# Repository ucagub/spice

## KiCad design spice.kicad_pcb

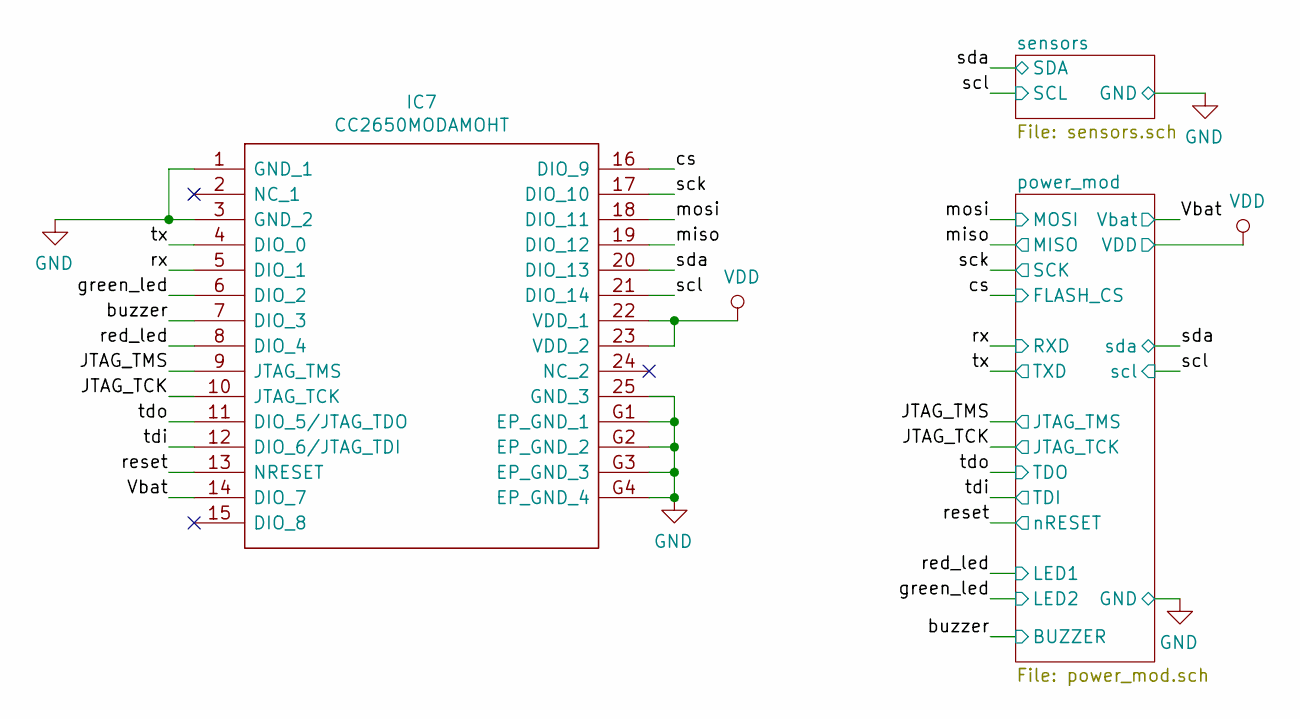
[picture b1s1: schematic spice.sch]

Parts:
IC7: CC2650MODAMOHT

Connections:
/JTAG_TCK: IC7.10 (JTAG_TCK); also elsewhere on the board
/JTAG_TMS: IC7.9 (JTAG_TMS); also elsewhere on the board
/Vbat: IC7.14 (DIO_7); also elsewhere on the board
/buzzer: IC7.7 (DIO_3); also elsewhere on the board
/cs: IC7.16 (DIO_9); also elsewhere on the board
/green_led: IC7.6 (DIO_2); also elsewhere on the board
/miso: IC7.19 (DIO_12); also elsewhere on the board
/mosi: IC7.18 (DIO_11); also elsewhere on the board
/red_led: IC7.8 (DIO_4); also elsewhere on the board
/reset: IC7.13 (NRESET); also elsewhere on the board
/rx: IC7.5 (DIO_1); also elsewhere on the board
/sck: IC7.17 (DIO_10); also elsewhere on the board
/scl: IC7.21 (DIO_14); also elsewhere on the board
/sda: IC7.20 (DIO_13); also elsewhere on the board
/tdi: IC7.12 (DIO_6/JTAG_TDI); also elsewhere on the board
/tdo: IC7.11 (DIO_5/JTAG_TDO); also elsewhere on the board
/tx: IC7.4 (DIO_0); also elsewhere on the board
GND: IC7.1 (GND_1), IC7.3 (GND_2), IC7.25 (GND_3), IC7.G1 (EP_GND_1), IC7.G2 (EP_GND_2), IC7.G3 (EP_GND_3), IC7.G4 (EP_GND_4); also elsewhere on the board
VDD: IC7.22 (VDD_1), IC7.23 (VDD_2); also elsewhere on the board

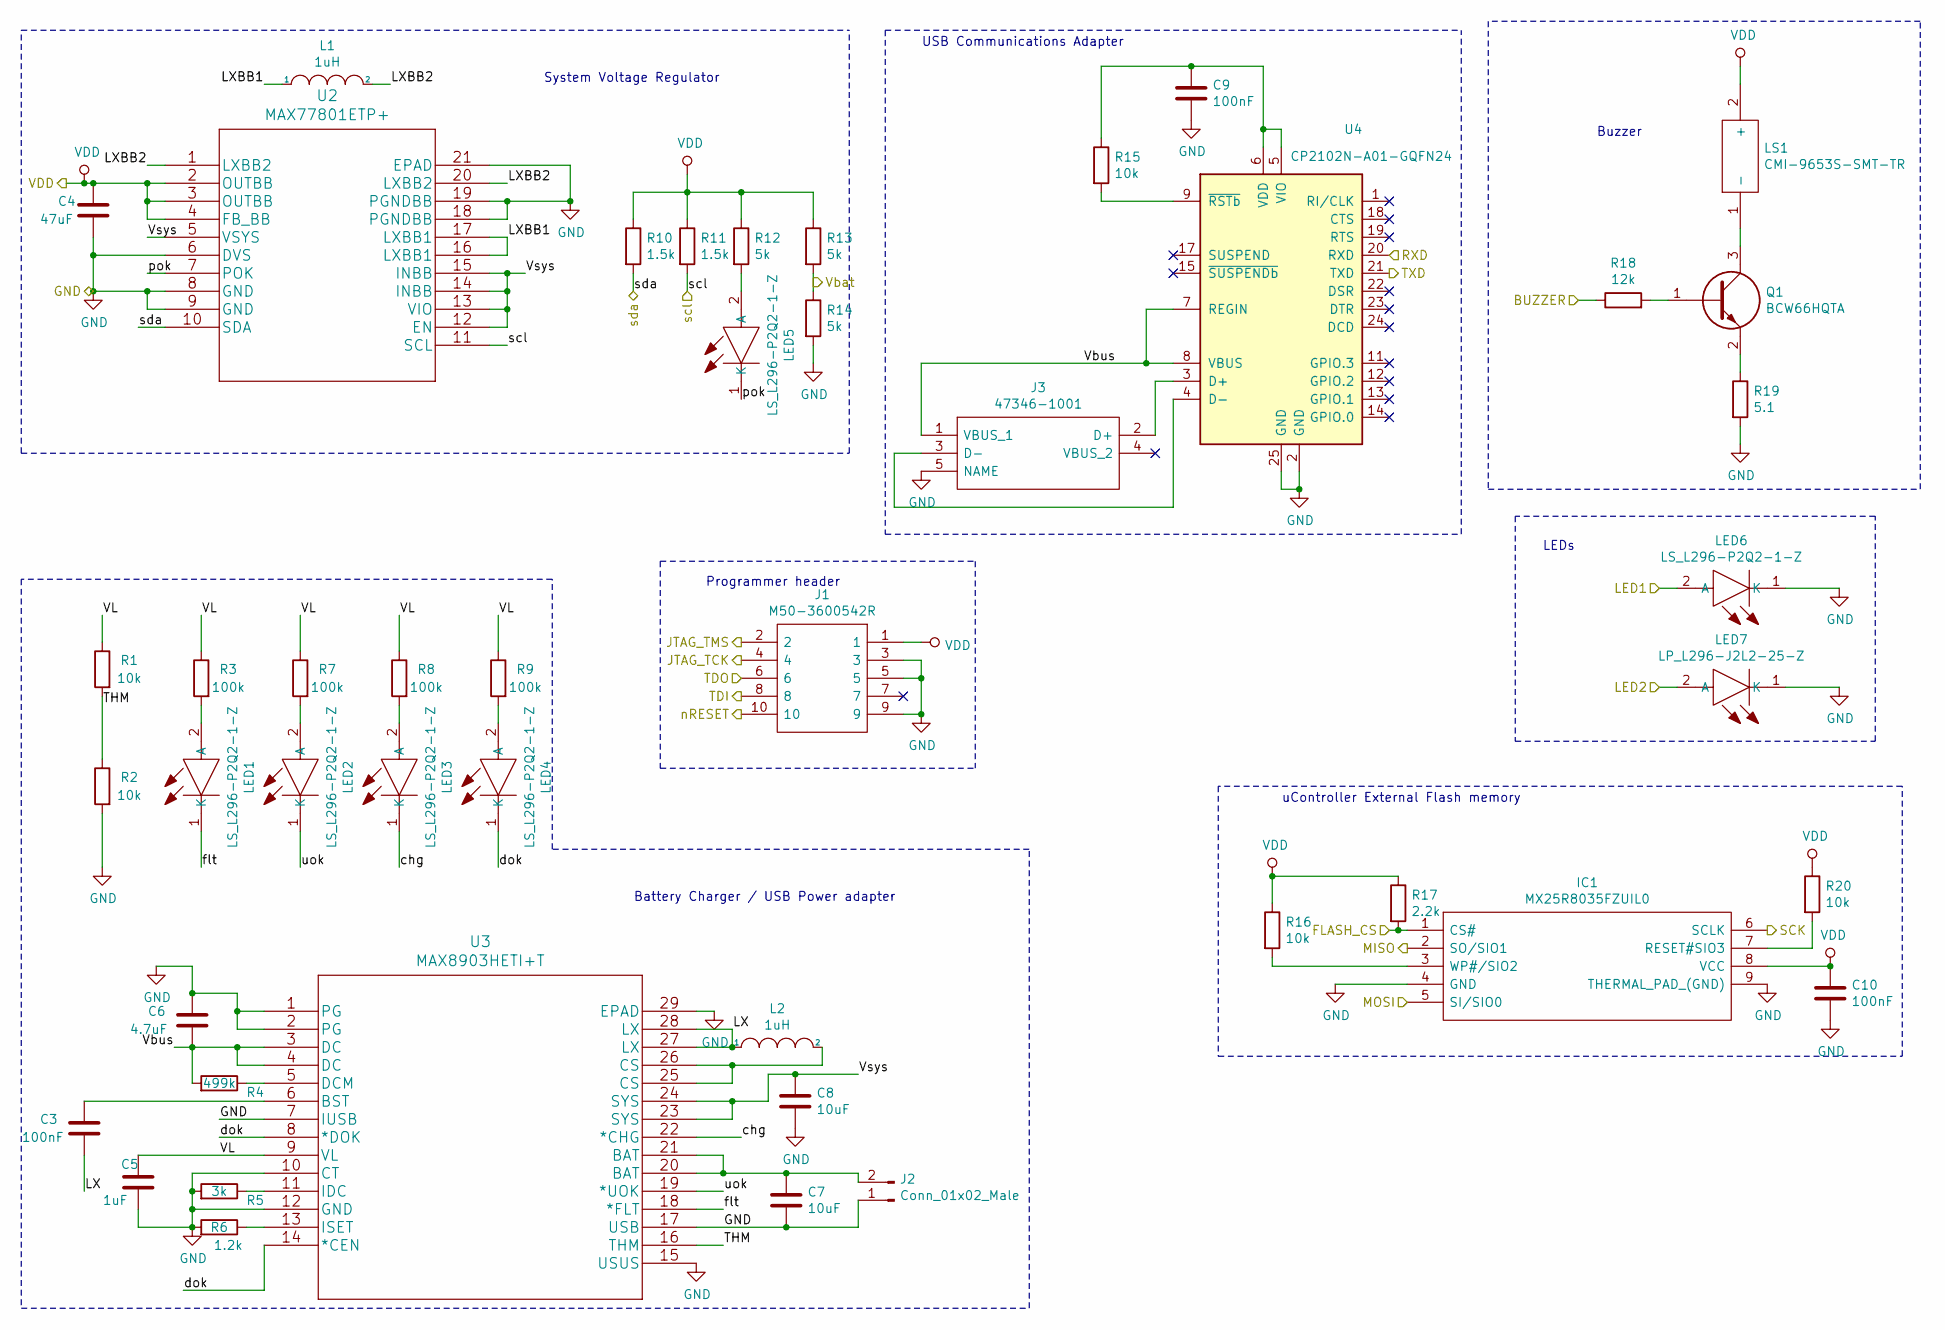
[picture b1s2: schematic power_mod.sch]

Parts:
C3, C9, C10: 100nF; CAPC1608X90N
C4: 47uF; CAPC1608X90N
C5: 1uF; CAPC1608X90N
C6: 4.7uF; CAPC1608X90N
C7, C8: 10uF; CAPC1608X90N
IC1: MX25R8035FZUIL0; USON-8L; Manufacturer_Part_Number MX25R8035FZUIL0
J1: M50-3600542R; M503600542R; Mouser Part Number 855-M50-3600542R
J2: Conn_01x02_Male; TSM10201LSVA
J3: 47346-1001; 47491-0001; Mouser Part Number 538-47346-1001
L1, L2: 1uH; INDPM2520X120N
LED1, LED2, LED3, LED4, LED5, LED6: LS_L296-P2Q2-1-Z; LEDC1707X85N; Mouser Part Number 720-LSL296-P2Q2-1-Z
LED7: LP_L296-J2L2-25-Z; LEDC1707X85N; Mouser Part Number 720-LPL296J2L225Z
LS1: CMI-9653S-SMT-TR; CMI9653SSMTTR; Mouser Part Number 490-CMI-9653S-SMT-TR
Q1: BCW66HQTA; FMMT619TA; Mouser Part Number 621-BCW66HQTA
R1, R2, R15, R16, R20: 10k; RESC1608X55N
R3, R7, R8, R9: 100k; RESC1608X55N
R4: 499k; RESC1608X55N
R5: 3k; RESC1608X55N
R6: 1.2k; RESC1608X55N
R10, R11: 1.5k; RESC1608X55N
R12, R13, R14: 5k; RESC1608X55N
R17: 2.2k; RESC1608X55N
R18: 12k; RESC1608X55N
R19: 5.1; RESC1608X55N
U2: MAX77801ETP+; MAX77801ETP&plus_
U3: MAX8903HETI+T; MAX8903HETI
U4: CP2102N-A01-GQFN24; QFN-24-1EP_4x4mm_P0.5mm_EP2.6x2.6mm

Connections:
/JTAG_TCK: J1.4; also elsewhere on the board
/JTAG_TMS: J1.2; also elsewhere on the board
/Vbat: R13.2, R14.1; also elsewhere on the board
/buzzer: R18.1; also elsewhere on the board
/cs: IC1.1 (CS#), R17.2; also elsewhere on the board
/green_led: LED7.2 (A); also elsewhere on the board
/miso: IC1.2 (SO/SIO1); also elsewhere on the board
/mosi: IC1.5 (SI/SIO0); also elsewhere on the board
/power_mod/LX: C3.2, L2.1, U3.27 (LX), U3.28 (LX)
/power_mod/LXBB1: L1.1, U2.16 (LXBB1), U2.17 (LXBB1)
/power_mod/LXBB2: L1.2, U2.1 (LXBB2), U2.20 (LXBB2)
/power_mod/THM: R1.2, R2.1, U3.16 (THM)
/power_mod/VL: C5.1, R1.1, R3.1, R7.1, R8.1, R9.1, U3.9 (VL)
/power_mod/Vbus: C6.2, J3.1 (VBUS_1), R4.2, U3.3 (DC), U3.4 (DC), U4.7 (REGIN), U4.8 (VBUS)
/power_mod/Vsys: C8.1, U2.5 (VSYS), U2.12 (EN), U2.13 (VIO), U2.14 (INBB), U2.15 (INBB), U3.23 (SYS), U3.24 (SYS)
/power_mod/chg: LED3.1 (K), U3.22 (*CHG)
/power_mod/dok: LED4.1 (K), U3.8 (*DOK), U3.14 (*CEN)
/power_mod/flt: LED1.1 (K), U3.18 (*FLT)
/power_mod/pok: LED5.1 (K), U2.7 (POK)
/power_mod/uok: LED2.1 (K), U3.19 (*UOK)
/red_led: LED6.2 (A); also elsewhere on the board
/reset: J1.10; also elsewhere on the board
/rx: U4.20 (RXD); also elsewhere on the board
/sck: IC1.6 (SCLK); also elsewhere on the board
/scl: R11.2, U2.11 (SCL); also elsewhere on the board
/sda: R10.2, U2.10 (SDA); also elsewhere on the board
/tdi: J1.8; also elsewhere on the board
/tdo: J1.6; also elsewhere on the board
/tx: U4.21 (TXD); also elsewhere on the board
GND: C4.2, C5.2, C6.1, C7.2, C8.2, C9.2, C10.2, IC1.4 (GND), IC1.9 (THERMAL_PAD_(GND)), J1.3, J1.5, J1.9, J2.1, J3.5 (NAME), LED6.1 (K), LED7.1 (K), R2.2, R5.2, R6.2, R14.2, R19.2, U2.6 (DVS), U2.8 (GND), U2.9 (GND), U2.18 (PGNDBB), U2.19 (PGNDBB), U2.21 (EPAD), U3.1 (PG), U3.2 (PG), U3.7 (IUSB), U3.10 (CT), U3.12 (GND), U3.15 (USUS), U3.17 (USB), U3.29 (EPAD), U4.2 (GND), U4.25 (GND); also elsewhere on the board
unnamed: C3.1, U3.6 (BST)
unnamed: C7.1, J2.2, U3.20 (BAT), U3.21 (BAT)
unnamed: C9.1, R15.1, U4.5 (VIO), U4.6 (VDD)
unnamed: IC1.3 (WP#/SIO2), R16.2
unnamed: IC1.7 (RESET#SIO3), R20.2
unnamed: J3.2 (D+), U4.3 (D+)
unnamed: J3.3 (D-), U4.4 (D-)
unnamed: L2.2, U3.25 (CS), U3.26 (CS)
unnamed: LED1.2 (A), R3.2
unnamed: LED2.2 (A), R7.2
unnamed: LED3.2 (A), R8.2
unnamed: LED4.2 (A), R9.2
unnamed: LED5.2 (A), R12.2
unnamed: LS1.1 (-), Q1.3
unnamed: Q1.1, R18.2
unnamed: Q1.2, R19.1
unnamed: R4.1, U3.5 (DCM)
unnamed: R5.1, U3.11 (IDC)
unnamed: R6.1, U3.13 (ISET)
unnamed: R15.2, U4.9 (~RSTb)
VDD: C4.1, C10.1, IC1.8 (VCC), J1.1, LS1.2 (+), R10.1, R11.1, R12.1, R13.1, R16.1, R17.1, R20.1, U2.2 (OUTBB), U2.3 (OUTBB), U2.4 (FB_BB); also elsewhere on the board

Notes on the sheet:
Battery Charger / USB Power adapter
System Voltage Regulator
Buzzer
LEDs
uController External Flash memory
Programmer header
USB Communications Adapter

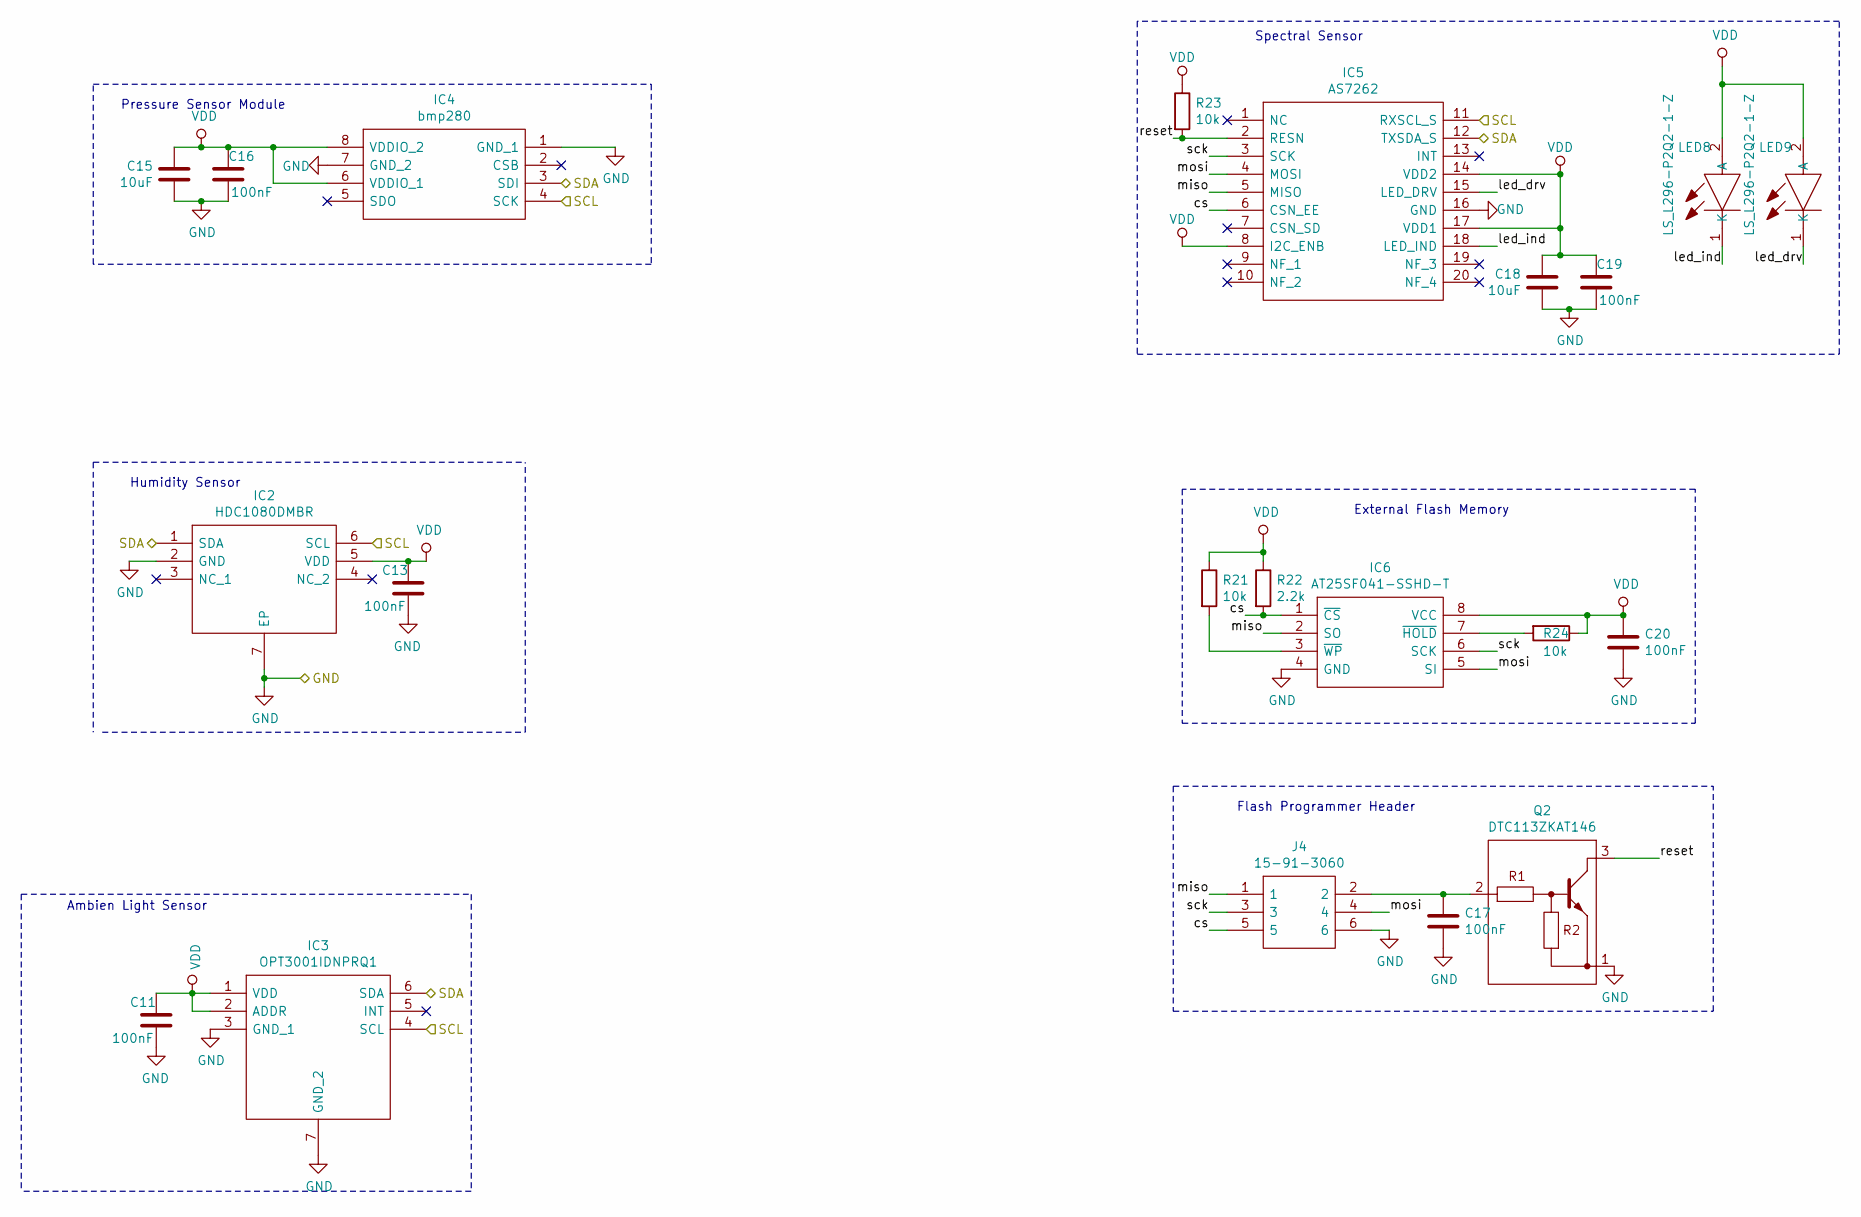
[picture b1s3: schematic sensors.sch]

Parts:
C11, C13, C16, C17, C19, C20: 100nF; CAPC1608X90N
C15, C18: 10uF; CAPC1608X90N
IC2: HDC1080DMBR; SON100P300X300X80-7N-D; Mouser Part Number 595-HDC1080DMBR
IC3: OPT3001IDNPRQ1; SON65P200X200X65-7N-D; Mouser Part Number 595-OPT3001IDNPRQ1
IC4: bmp280; 8-PIN-METAL-LID-LGA; Mouser Part Number 262-BMP280
IC5: AS7262; AMS_LGA-20; Mouser Part Number 985-AS7262
IC6: AT25SF041-SSHD-T; SOIC127P600X175-8N; Mouser Part Number 988-AT25SF041-SSHD-T
J4: 15-91-3060; 15913060; Mouser Part Number 538-15-91-3060
LED8, LED9: LS_L296-P2Q2-1-Z; LEDC1707X85N; Mouser Part Number 720-LSL296-P2Q2-1-Z
Q2: DTC113ZKAT146; DTB123YKT146; Mouser Part Number 755-DTC113ZKAT146
R21, R23, R24: 10k; RESC1608X55N
R22: 2.2k; RESC1608X55N

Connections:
/scl: IC2.6 (SCL), IC3.4 (SCL), IC4.4 (SCK), IC5.11 (RXSCL_S); also elsewhere on the board
/sda: IC2.1 (SDA), IC3.6 (SDA), IC4.3 (SDI), IC5.12 (TXSDA_S); also elsewhere on the board
/sensors/cs: IC5.6 (CSN_EE), IC6.1 (~CS), J4.5, R22.2
/sensors/led_drv: IC5.15 (LED_DRV), LED9.1 (K)
/sensors/led_ind: IC5.18 (LED_IND), LED8.1 (K)
/sensors/miso: IC5.5 (MISO), IC6.2 (SO), J4.1
/sensors/mosi: IC5.4 (MOSI), IC6.5 (SI), J4.4
/sensors/reset: IC5.2 (RESN), Q2.3, R23.2
/sensors/sck: IC5.3 (SCK), IC6.6 (SCK), J4.3
GND: C11.2, C13.2, C15.2, C16.2, C17.2, C18.2, C19.2, C20.2, IC2.2 (GND), IC2.7 (EP), IC3.3 (GND_1), IC3.7 (GND_2), IC4.1 (GND_1), IC4.7 (GND_2), IC5.16 (GND), IC6.4 (GND), J4.6, Q2.1; also elsewhere on the board
unnamed: C17.1, J4.2, Q2.2
unnamed: IC6.3 (~WP), R21.2
unnamed: IC6.7 (~HOLD), R24.2
VDD: C11.1, C13.1, C15.1, C16.1, C18.1, C19.1, C20.1, IC2.5 (VDD), IC3.1 (VDD), IC3.2 (ADDR), IC4.6 (VDDIO_1), IC4.8 (VDDIO_2), IC5.8 (I2C_ENB), IC5.14 (VDD2), IC5.17 (VDD1), IC6.8 (VCC), LED8.2 (A), LED9.2 (A), R21.1, R22.1, R23.1, R24.1; also elsewhere on the board

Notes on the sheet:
Pressure Sensor Module
Humidity Sensor
Ambien Light Sensor
External Flash Memory
Flash Programmer Header
Spectral Sensor

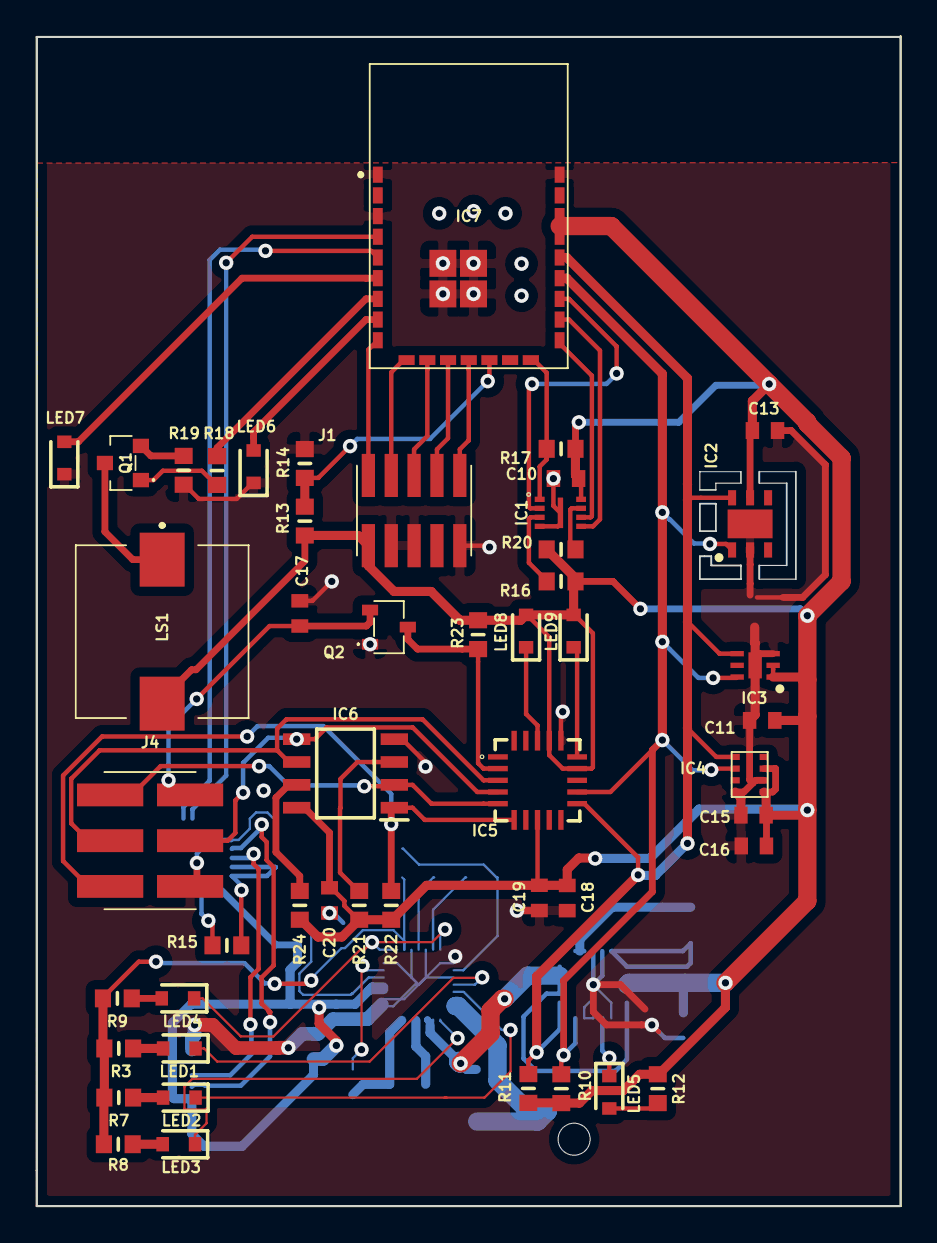
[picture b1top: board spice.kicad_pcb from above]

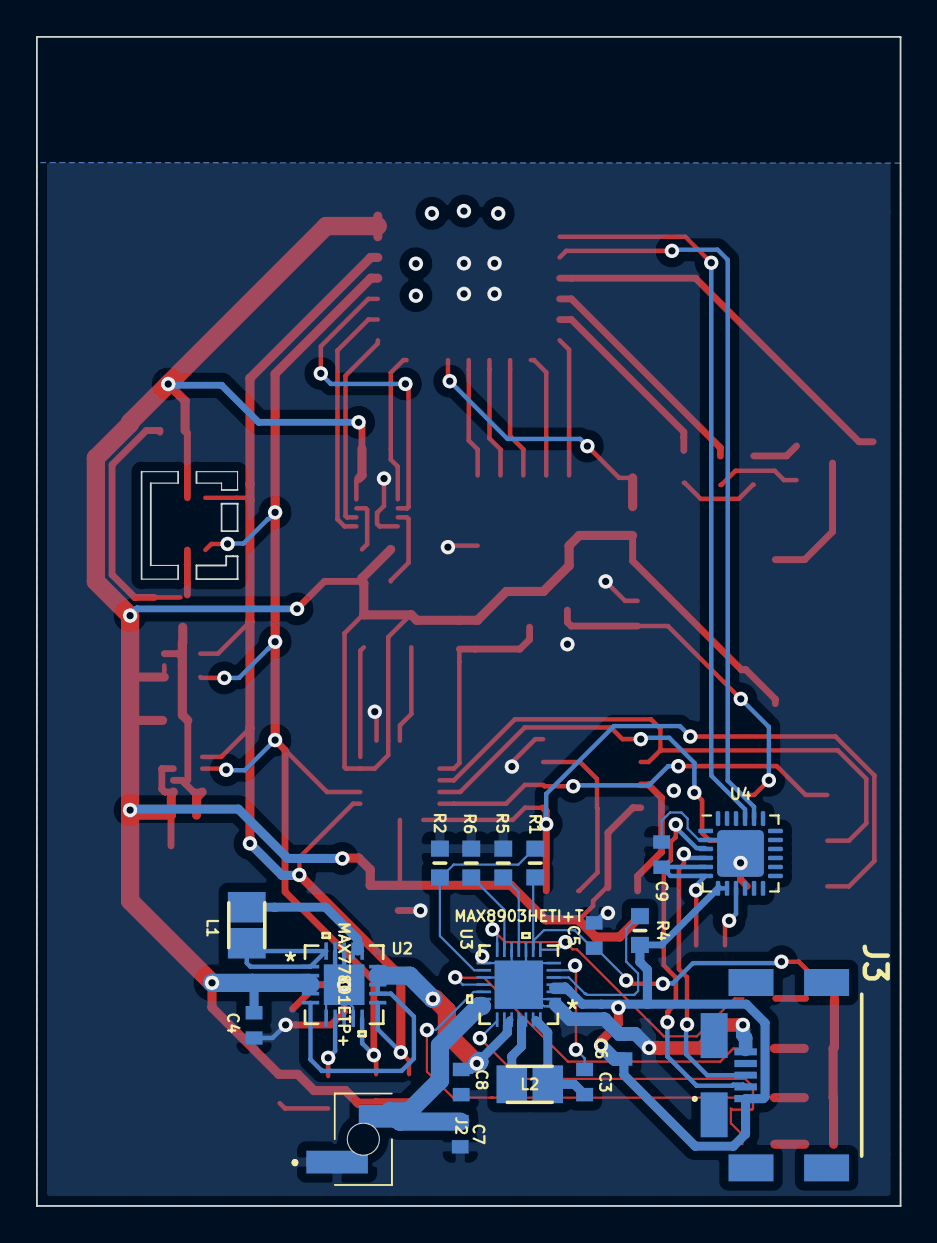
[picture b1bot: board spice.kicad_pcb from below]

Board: 2 copper layers, 48.0 x 64.9 mm, 68 parts (19 on the bottom side), 61 nets.

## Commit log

2020-02-11 actual files
    initial commit
2020-02-11 deleted all
2020-02-11 added all files

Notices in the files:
parts and their libraries:
Copyright 2016 Accelerated Designs. All rights reserved.
